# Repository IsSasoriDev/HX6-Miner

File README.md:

# HX-6

A 6 chip BM1370 Bitcoin miner board with a touchscreen, made in KiCad.

Six BM1370s (the chip from the Antminer S21 Pro) sit under one normal desktop CPU cooler, powered by a 4 phase VRM off 12 V. An ESP32-S3 runs it over WiFi and drives a 2.8" touch display.

## Specs

| | |
|---|---|
| ASICs | 6x BM1370 on one core rail |
| Expected hashrate | about 6 to 7 TH/s at stock settings |
| Power | 12 V in through XT60, around 100 to 110 W |
| Core VRM | TI TPS53647, 4 phases with CSD95490Q5MC power stages |
| Controller | ESP32-S3-WROOM-1 (N16R8), USB-C for flashing |
| Screen | Waveshare 2.8" capacitive touch LCD (ST7789 + CST328), plugs into the 13 pin GH1.25 socket |
| Cooling | any Intel LGA115x / 1200 CPU cooler, 2 PWM fan headers |
| Board | 6 layers, 170 x 115 mm |

## Status

Rev B. Fully routed, DRC clean in KiCad 7, Gerbers ready for JLCPCB.

**Not built or tested yet.** Treat it as a first prototype. If you build one, open an issue and tell me how it went.

## Layout

The board reads left to right: 12 V input, the four VRM phases, the ASIC block, then the ESP32, buttons, display socket and USB. The small 5 V, 3.3 V, 1.2 V and 0.8 V rails run along the bottom edge.

The six chips are in a 3 x 2 grid that fits inside a 46 x 46 mm square, so one cooler base covers all of them. The data chain goes 1 → 2 → 3 along the top row and comes back 4 → 5 → 6 along the bottom. Only the chips are on the top side under the cooler. All their capacitors are on the back, right under each chip.

## Schematic

Four sheets: power input and rails, core VRM, ASIC chain, and controller / display / fans.

## Files

```
hx6.kicad_pro          KiCad project (open this)
hx6.kicad_pcb          the board
*.kicad_sch            schematic sheets
hx6.kicad_sym          custom symbols
hx6.pretty/            custom footprints (BM1370, power stage, cooler hole)
fab/                   Gerber zip, BOM and CPL for JLCPCB
docs/                  images and design notes
```

It was made in KiCad 7 and opens fine in KiCad 8, 9 and 10.

## Ordering

Upload `fab/HX6_revB_gerbers_JLCPCB.zip` to JLCPCB and pick:

- 6 layers, 1.6 mm, ENIG
- 2 oz inner copper (the core rail pulls about 100 A)
- epoxy filled and capped vias. There are vias inside the chip pads and they need this.

For assembly, add `fab/HX6_revB_BOM_JLCPCB.csv` and `fab/HX6_revB_CPL_JLCPCB.csv` and match the LCSC parts in their tool. JLCPCB doesn't stock the BM1370, so you'll have to supply those or solder them yourself. Check the part rotations in their preview, especially on the bottom side.

## Before you order

- Run DRC once more in your KiCad version.
- The VRM compensation values are a starting point. Check the core rail at low load before you put real load on it.
- The 25 MHz oscillator has to be a 1.2 V part (Taitien OXLTDLJANF-25.000000 or similar).
- R20 is not fitted on purpose. VR_HOT on the VRM controller isn't used.

## Firmware

AxeForge is the default but [ESP-Miner-NerdQAxePlus](https://github.com/shufps/ESP-Miner-NerdQAxePlus) also supports 6x BM1370 with the same TPS53647 VRM, so a port mostly needs this board's pin map (in [docs/design-notes.md](docs/design-notes.md)) and drivers for the 2.8" screen and the CST328 touch chip.

## Credits

Bitmain doesn't publish a BM1370 datasheet. The pin map and footprint come from the open hardware work in [shufps/qaxe](https://github.com/shufps/qaxe) (NerdQAxe++). Check their license if you reuse those parts. The rest of the board was designed for this project.

Full technical notes (pin map, I2C addresses, layer stack, part choices) are in [docs/design-notes.md](docs/design-notes.md).

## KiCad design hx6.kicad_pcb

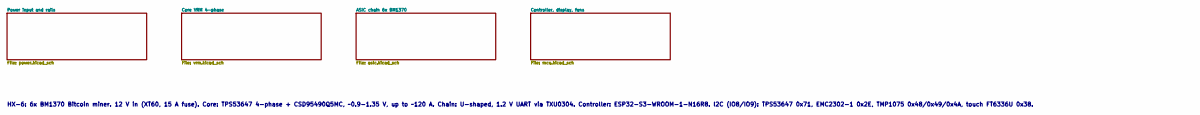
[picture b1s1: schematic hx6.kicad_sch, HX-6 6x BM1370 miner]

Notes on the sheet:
HX-6: 6x BM1370 Bitcoin miner. 12 V in (XT60, 15 A fuse). Core: TPS53647 4-phase + CSD95490Q5MC, ~0.9-1.35 V, up to ~120 A. Chain: U-shaped, 1.2 V UART via TXU0304. Controller: ESP32-S3-WROOM-1-N16R8. I2C (IO8/IO9): TPS53647 0x71, EMC2302-1 0x2E, TMP1075 0x48/0x49/0x4A, touch FT6336U 0x38.

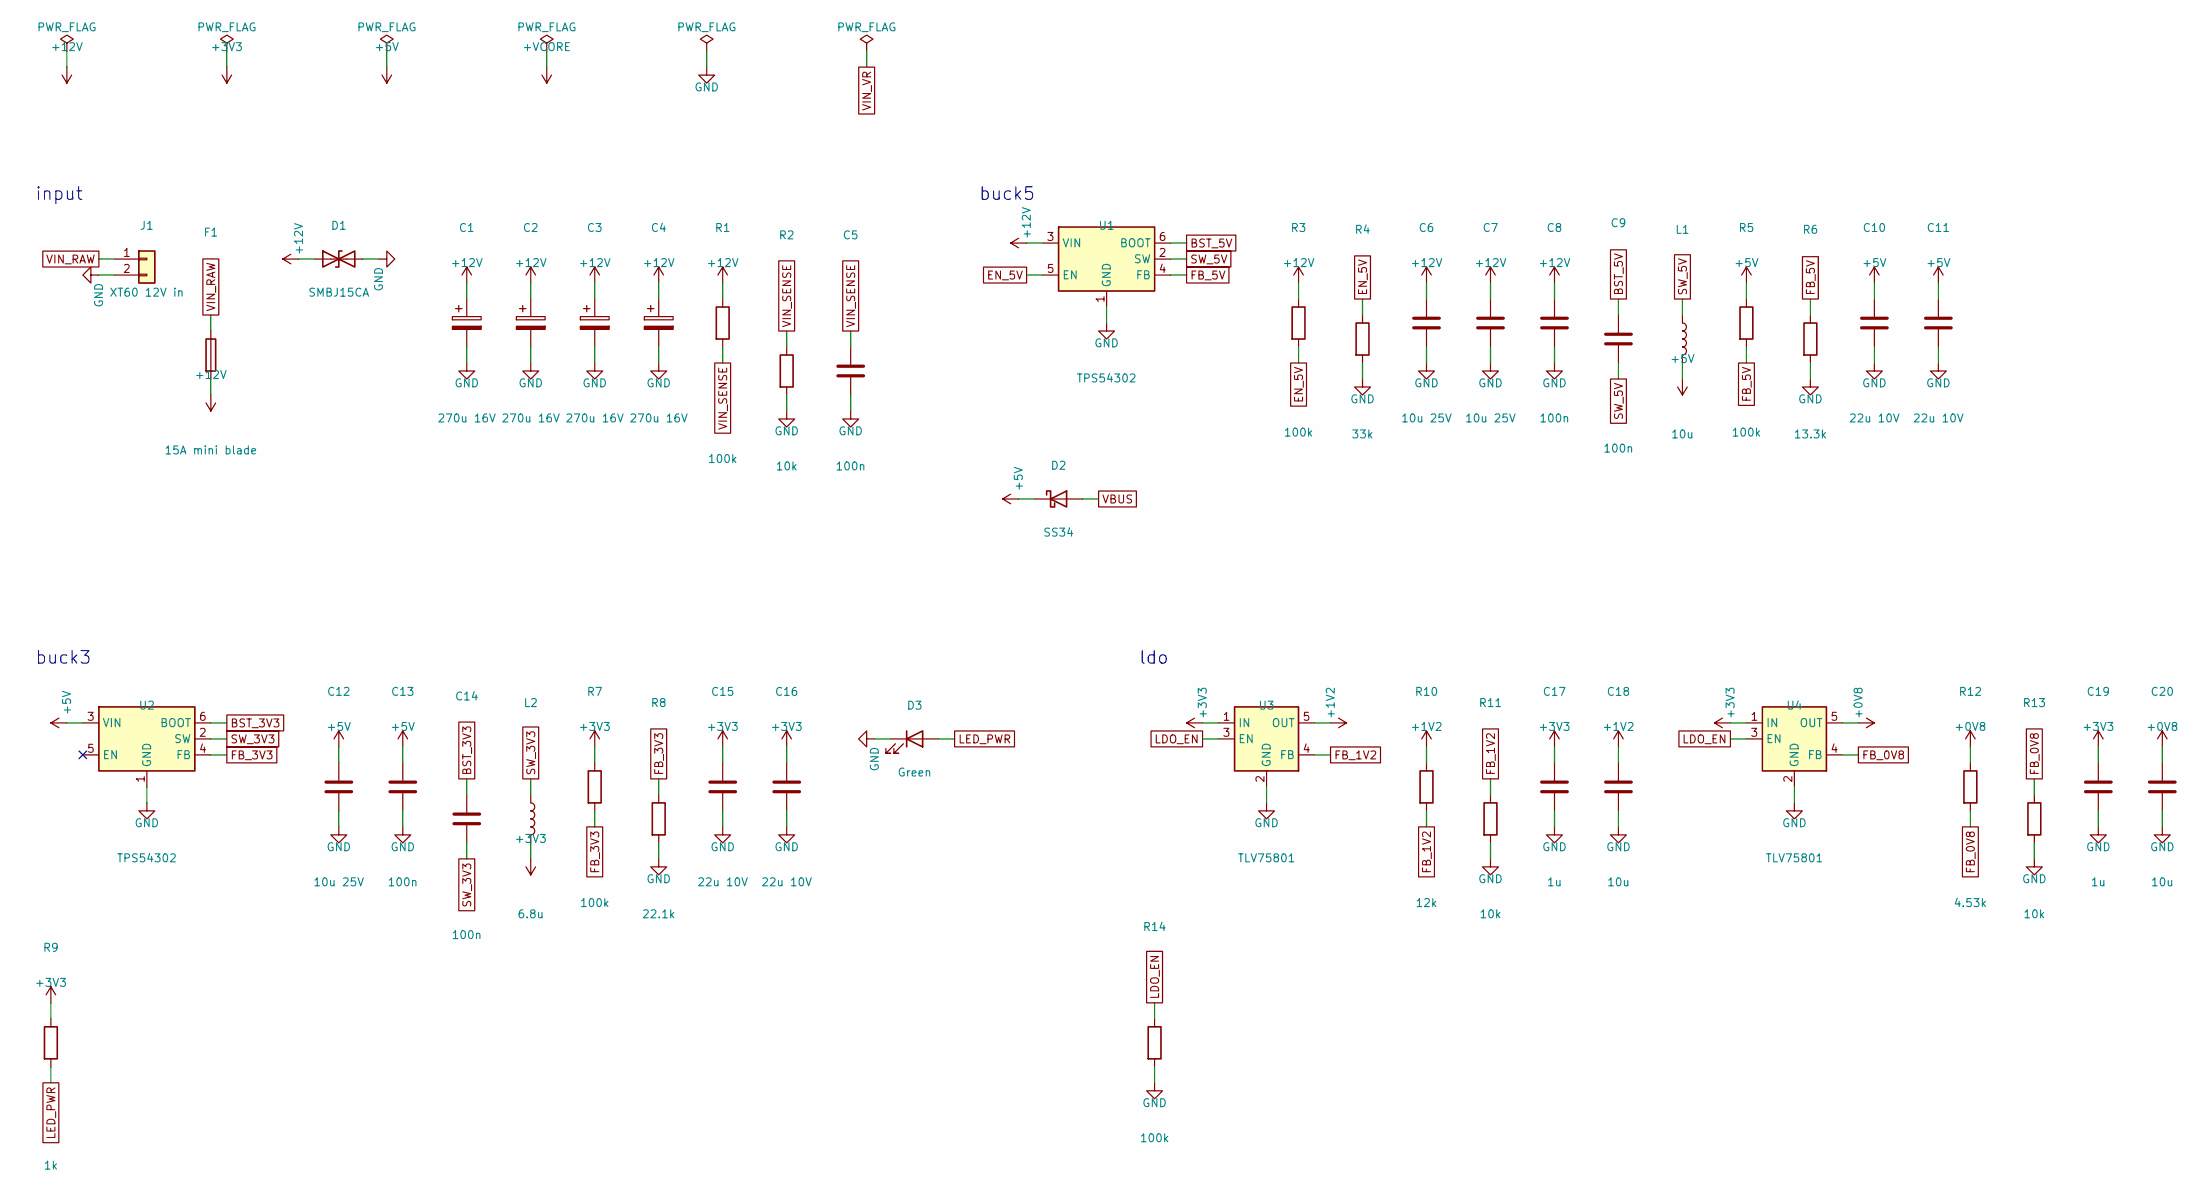
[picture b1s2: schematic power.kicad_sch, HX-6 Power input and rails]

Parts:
C1, C2, C3, C4: 270u 16V; CP_Elec_8x10; MPN Panasonic 16SVPF270M (polymer)
C5, C8, C9, C13, C14: 100n; C_0402_1005Metric
C6, C7, C12: 10u 25V; C_1206_3216Metric
C10, C11, C15, C16: 22u 10V; C_0805_2012Metric
C17, C19: 1u; C_0603_1608Metric
C18, C20: 10u; C_0805_2012Metric
D1: SMBJ15CA; D_SMB; MPN SMBJ15CA (bidirectional)
D2: SS34; D_SMA; MPN SS34
D3: Green; LED_0603_1608Metric
F1: 15A mini blade; Fuseholder_Blade_Mini_Keystone_3568; MPN Keystone 3568 holder + 15 A mini blade 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
J1: XT60 12V in; AMASS_XT60-M_1x02_P7.20mm_Vertical; MPN AMASS XT60PW-M (vertical)
L1: 10u; L_Bourns_SRP7028A_7.3x6.6mm; MPN Bourns SRP7028A-100M
L2: 6.8u; L_Bourns_SRP7028A_7.3x6.6mm; MPN Bourns SRP7028A-6R8M
R1, R3, R5, R7, R14: 100k; R_0402_1005Metric
R2, R11, R13: 10k; R_0402_1005Metric
R4: 33k; R_0402_1005Metric
R6: 13.3k; R_0402_1005Metric
R8: 22.1k; R_0402_1005Metric
R9: 1k; R_0402_1005Metric
R10: 12k; R_0402_1005Metric
R12: 4.53k; R_0402_1005Metric
U1, U2: TPS54302; SOT-23-6; MPN TPS54302DDCR
U3, U4: TLV75801; SOT-23-5; MPN TLV75801PDBVR

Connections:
+0V8: C20.1, R12.1, U4.5 (OUT); also elsewhere on the board
+1V2: C18.1, R10.1, U3.5 (OUT); also elsewhere on the board
+3V3: C15.1, C16.1, C17.1, C19.1, L2.2, R7.1, R9.1, U3.1 (IN), U4.1 (IN); also elsewhere on the board
+5V: C10.1, C11.1, C12.1, C13.1, D2.1 (K), L1.2, R5.1, U2.3 (VIN); also elsewhere on the board
+12V: C1.1, C2.1, C3.1, C4.1, C6.1, C7.1, C8.1, D1.1 (A1), F1.2, R1.1, R3.1, U1.3 (VIN); also elsewhere on the board
BST_3V3: C14.1, U2.6 (BOOT)
BST_5V: C9.1, U1.6 (BOOT)
EN_5V: R3.2, R4.1, U1.5 (EN)
FB_0V8: R12.2, R13.1, U4.4 (FB)
FB_1V2: R10.2, R11.1, U3.4 (FB)
FB_3V3: R7.2, R8.1, U2.4 (FB)
FB_5V: R5.2, R6.1, U1.4 (FB)
GND: C1.2, C2.2, C3.2, C4.2, C5.2, C6.2, C7.2, C8.2, C10.2, C11.2, C12.2, C13.2, C15.2, C16.2, C17.2, C18.2, C19.2, C20.2, D1.2 (A2), D3.1 (K), J1.2, R2.2, R4.2, R6.2, R8.2, R11.2, R13.2, R14.2, U1.1 (GND), U2.1 (GND), U3.2 (GND), U4.2 (GND); also elsewhere on the board
LDO_EN: R14.1, U3.3 (EN), U4.3 (EN); also elsewhere on the board
LED_PWR: D3.2 (A), R9.2
SW_3V3: C14.2, L2.1, U2.2 (SW)
SW_5V: C9.2, L1.1, U1.2 (SW)
VBUS: D2.2 (A); also elsewhere on the board
VIN_RAW: F1.1, J1.1
VIN_SENSE: C5.1, R1.2, R2.1; also elsewhere on the board

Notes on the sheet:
input
buck5
buck3
ldo

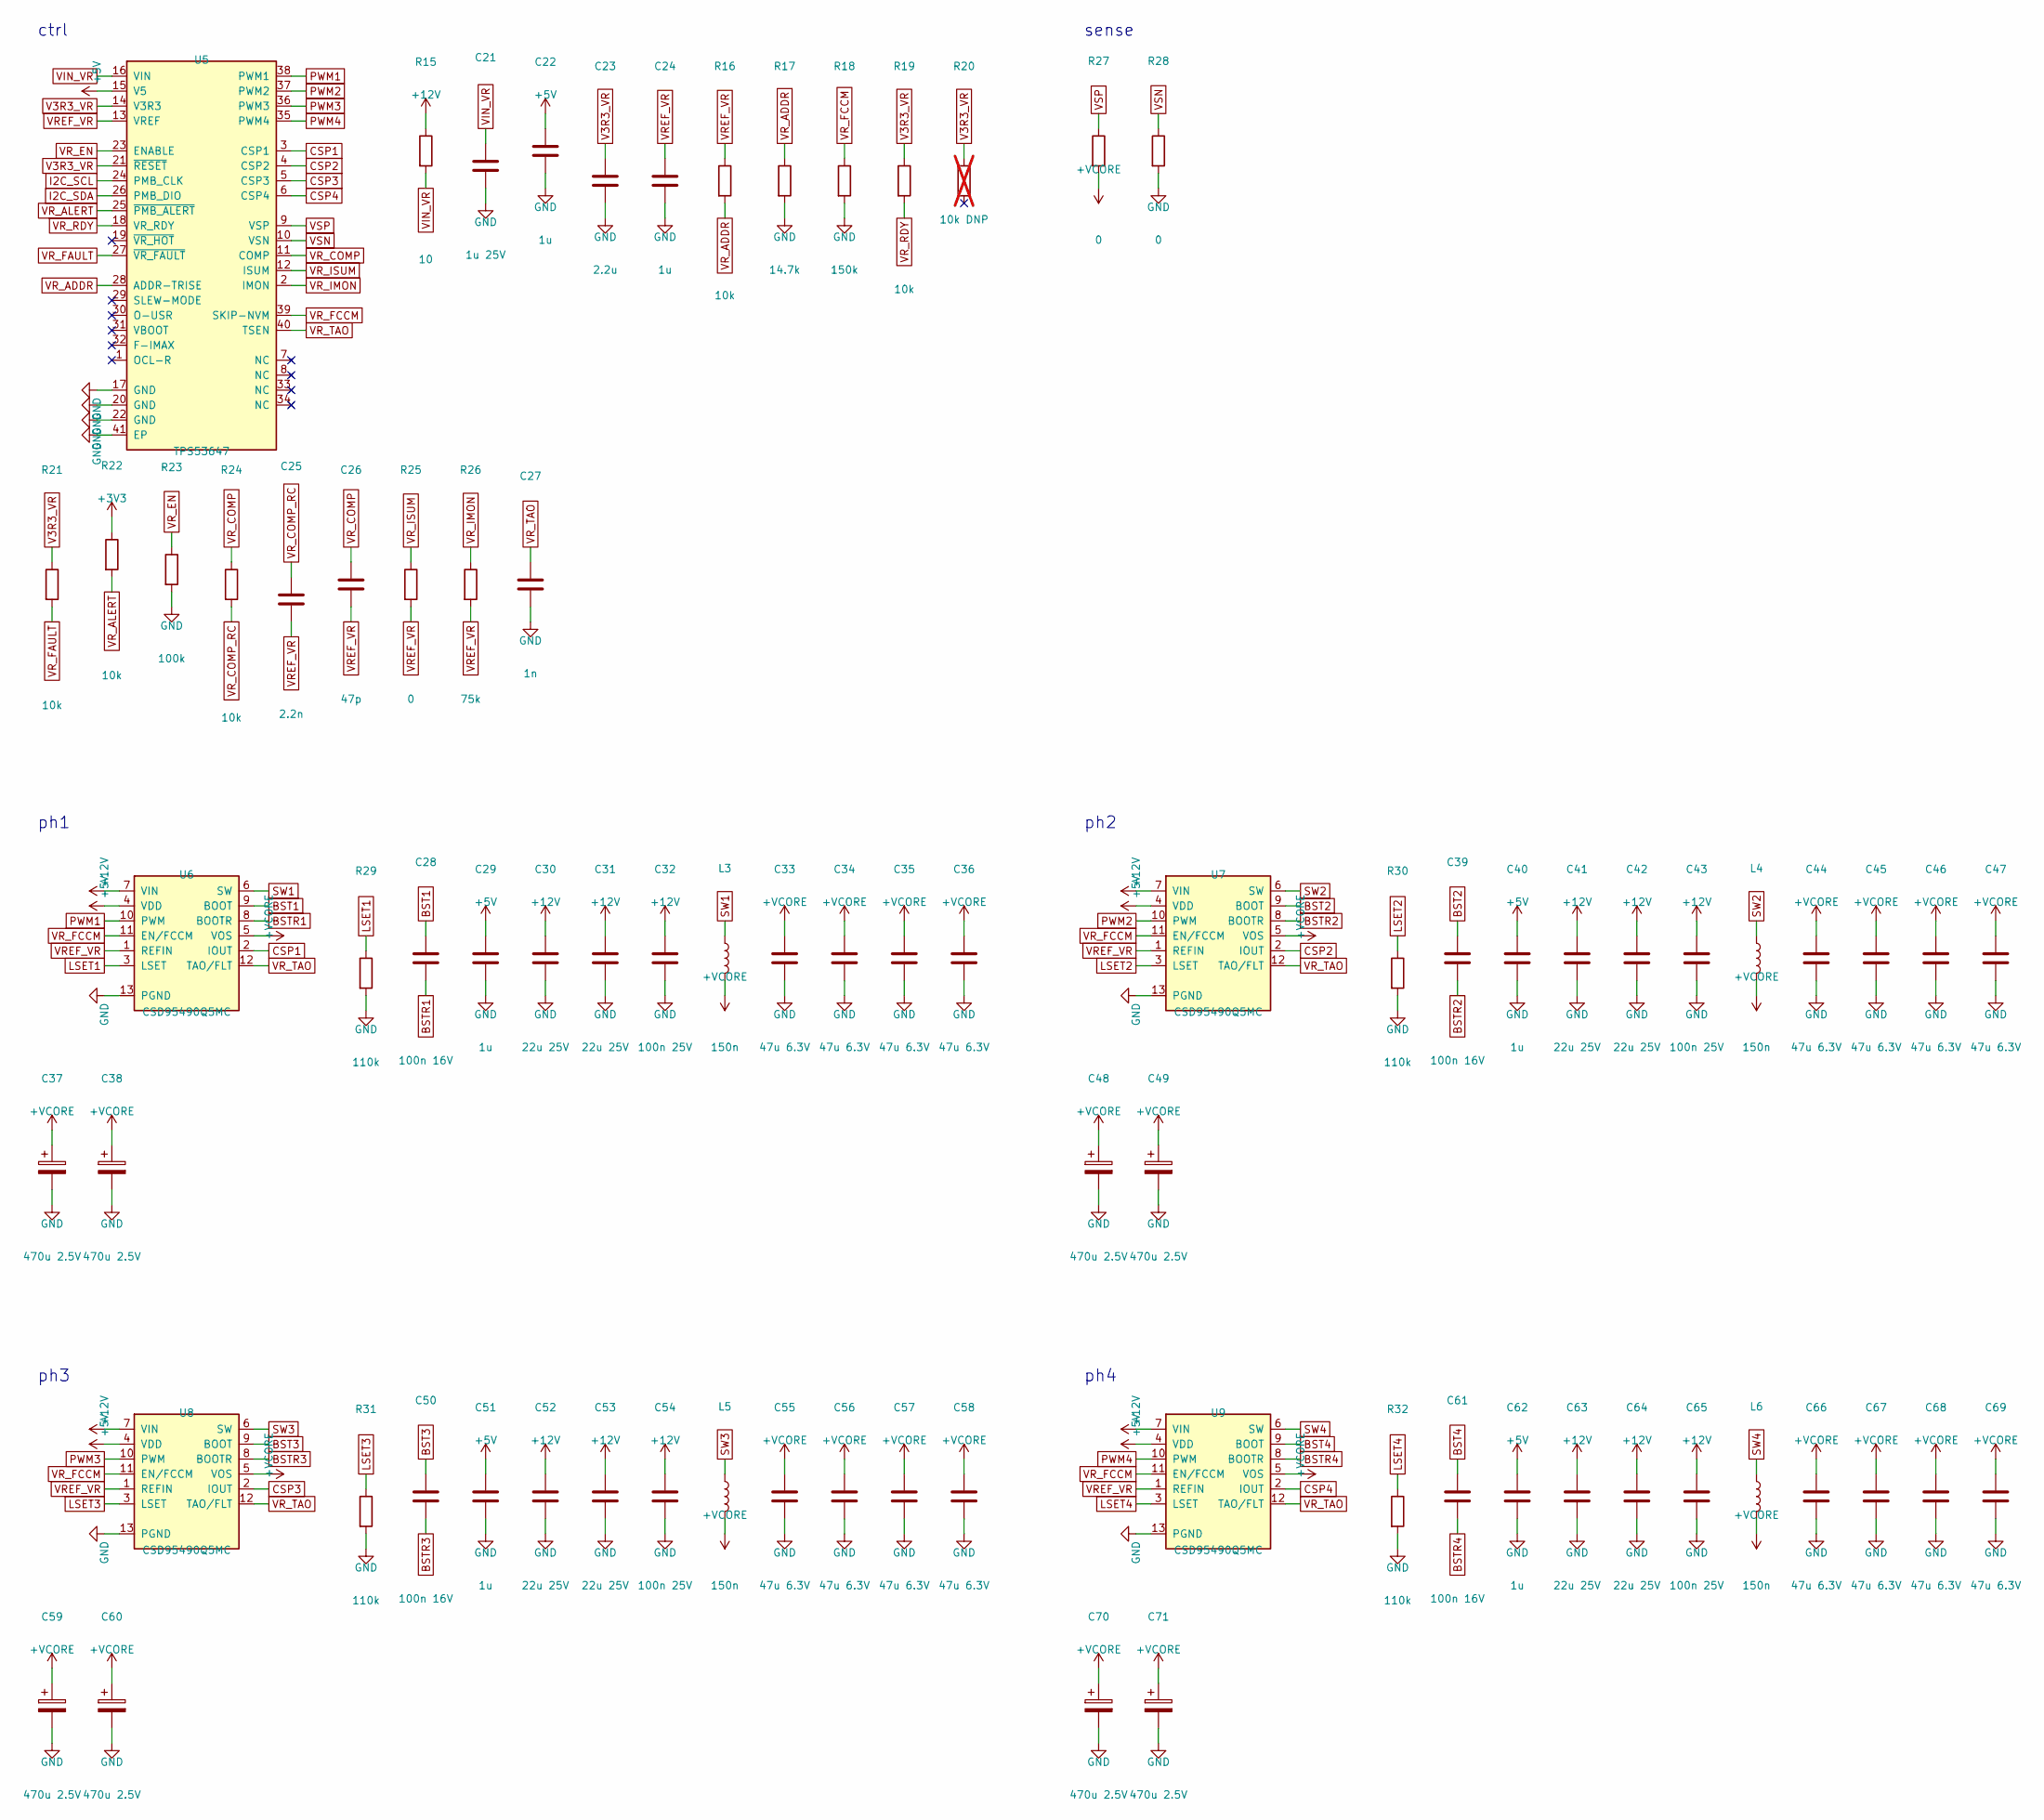
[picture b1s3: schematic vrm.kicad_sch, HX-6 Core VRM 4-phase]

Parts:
C21: 1u 25V; C_0603_1608Metric
C22, C24, C29, C40, C51, C62: 1u; C_0603_1608Metric
C23: 2.2u; C_0603_1608Metric
C25: 2.2n; C_0402_1005Metric
C26: 47p; C_0402_1005Metric
C27: 1n; C_0402_1005Metric
C28, C39, C50, C61: 100n 16V; C_0402_1005Metric
C30, C31, C41, C42, C52, C53, C63, C64: 22u 25V; C_1210_3225Metric
C32, C43, C54, C65: 100n 25V; C_0402_1005Metric
C33, C34, C35, C36, C44, C45, C46, C47, C55, C56, C57, C58, C66, C67, C68, C69: 47u 6.3V; C_1206_3216Metric
C37, C38, C48, C49, C59, C60, C70, C71: 470u 2.5V; CP_EIA-7343-31_Kemet-D; MPN Panasonic 2R5TPF470M6L (POSCAP)
L3, L4, L5, L6: 150n; L_Coilcraft_XAL7070-XXX; MPN Coilcraft XAL7070-151MEC
R15: 10; R_0603_1608Metric
R16, R19, R21, R22, R24: 10k; R_0402_1005Metric
R17: 14.7k; R_0402_1005Metric
R18: 150k; R_0402_1005Metric
R20: 10k DNP; R_0402_1005Metric; not fitted
R23: 100k; R_0402_1005Metric
R25, R27, R28: 0; R_0402_1005Metric
R26: 75k; R_0402_1005Metric
R29, R30, R31, R32: 110k; R_0402_1005Metric
U5: TPS53647; Texas_RHA0040B_VQFN-40-1EP_6x6mm_P0.5mm_EP4.15x4.15mm_Therm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; MPN TPS53647RTAR
U6, U7, U8, U9: CSD95490Q5MC; TI_DMC0012A_VSON-CLIP_5x6mm; MPN CSD95490Q5MC

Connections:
+3V3: R22.1; also elsewhere on the board
+5V: C22.1, C29.1, C40.1, C51.1, C62.1, U5.15 (V5), U6.4 (VDD), U7.4 (VDD), U8.4 (VDD), U9.4 (VDD); also elsewhere on the board
+12V: C30.1, C31.1, C32.1, C41.1, C42.1, C43.1, C52.1, C53.1, C54.1, C63.1, C64.1, C65.1, R15.1, U6.7 (VIN), U7.7 (VIN), U8.7 (VIN), U9.7 (VIN); also elsewhere on the board
+VCORE: C33.1, C34.1, C35.1, C36.1, C37.1, C38.1, C44.1, C45.1, C46.1, C47.1, C48.1, C49.1, C55.1, C56.1, C57.1, C58.1, C59.1, C60.1, C66.1, C67.1, C68.1, C69.1, C70.1, C71.1, L3.2, L4.2, L5.2, L6.2, R27.2, U6.5 (VOS), U7.5 (VOS), U8.5 (VOS), U9.5 (VOS); also elsewhere on the board
BST1: C28.1, U6.9 (BOOT)
BST2: C39.1, U7.9 (BOOT)
BST3: C50.1, U8.9 (BOOT)
BST4: C61.1, U9.9 (BOOT)
BSTR1: C28.2, U6.8 (BOOTR)
BSTR2: C39.2, U7.8 (BOOTR)
BSTR3: C50.2, U8.8 (BOOTR)
BSTR4: C61.2, U9.8 (BOOTR)
CSP1: U5.3 (CSP1), U6.2 (IOUT)
CSP2: U5.4 (CSP2), U7.2 (IOUT)
CSP3: U5.5 (CSP3), U8.2 (IOUT)
CSP4: U5.6 (CSP4), U9.2 (IOUT)
GND: C21.2, C22.2, C23.2, C24.2, C27.2, C29.2, C30.2, C31.2, C32.2, C33.2, C34.2, C35.2, C36.2, C37.2, C38.2, C40.2, C41.2, C42.2, C43.2, C44.2, C45.2, C46.2, C47.2, C48.2, C49.2, C51.2, C52.2, C53.2, C54.2, C55.2, C56.2, C57.2, C58.2, C59.2, C60.2, C62.2, C63.2, C64.2, C65.2, C66.2, C67.2, C68.2, C69.2, C70.2, C71.2, R17.2, R18.2, R23.2, R28.2, R29.2, R30.2, R31.2, R32.2, U5.17 (GND), U5.20 (GND), U5.22 (GND), U5.41 (EP), U6.13 (PGND), U7.13 (PGND), U8.13 (PGND), U9.13 (PGND); also elsewhere on the board
I2C_SCL: U5.24 (PMB_CLK); also elsewhere on the board
I2C_SDA: U5.26 (PMB_DIO); also elsewhere on the board
LSET1: R29.1, U6.3 (LSET)
LSET2: R30.1, U7.3 (LSET)
LSET3: R31.1, U8.3 (LSET)
LSET4: R32.1, U9.3 (LSET)
PWM1: U5.38 (PWM1), U6.10 (PWM)
PWM2: U5.37 (PWM2), U7.10 (PWM)
PWM3: U5.36 (PWM3), U8.10 (PWM)
PWM4: U5.35 (PWM4), U9.10 (PWM)
SW1: L3.1, U6.6 (SW)
SW2: L4.1, U7.6 (SW)
SW3: L5.1, U8.6 (SW)
SW4: L6.1, U9.6 (SW)
V3R3_VR: C23.1, R19.1, R20.1, R21.1, U5.14 (V3R3), U5.21 (~RESET)
VIN_VR: C21.1, R15.2, U5.16 (VIN)
VREF_VR: C24.1, C25.2, C26.2, R16.1, R25.2, R26.2, U5.13 (VREF), U6.1 (REFIN), U7.1 (REFIN), U8.1 (REFIN), U9.1 (REFIN)
VR_ADDR: R16.2, R17.1, U5.28 (ADDR-TRISE)
VR_ALERT: R22.2, U5.25 (~PMB_ALERT); also elsewhere on the board
VR_COMP: C26.1, R24.1, U5.11 (COMP)
VR_COMP_RC: C25.1, R24.2
VR_EN: R23.1, U5.23 (ENABLE); also elsewhere on the board
VR_FAULT: R21.2, U5.27 (~VR_FAULT)
VR_FCCM: R18.1, U5.39 (SKIP-NVM), U6.11 (EN/FCCM), U7.11 (EN/FCCM), U8.11 (EN/FCCM), U9.11 (EN/FCCM)
VR_IMON: R26.1, U5.2 (IMON)
VR_ISUM: R25.1, U5.12 (ISUM)
VR_RDY: R19.2, U5.18 (VR_RDY); also elsewhere on the board
VR_TAO: C27.1, U5.40 (TSEN), U6.12 (TAO/FLT), U7.12 (TAO/FLT), U8.12 (TAO/FLT), U9.12 (TAO/FLT)
VSN: R28.1, U5.10 (VSN)
VSP: R27.1, U5.9 (VSP)

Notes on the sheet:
ctrl
sense
ph1
ph2
ph3
ph4

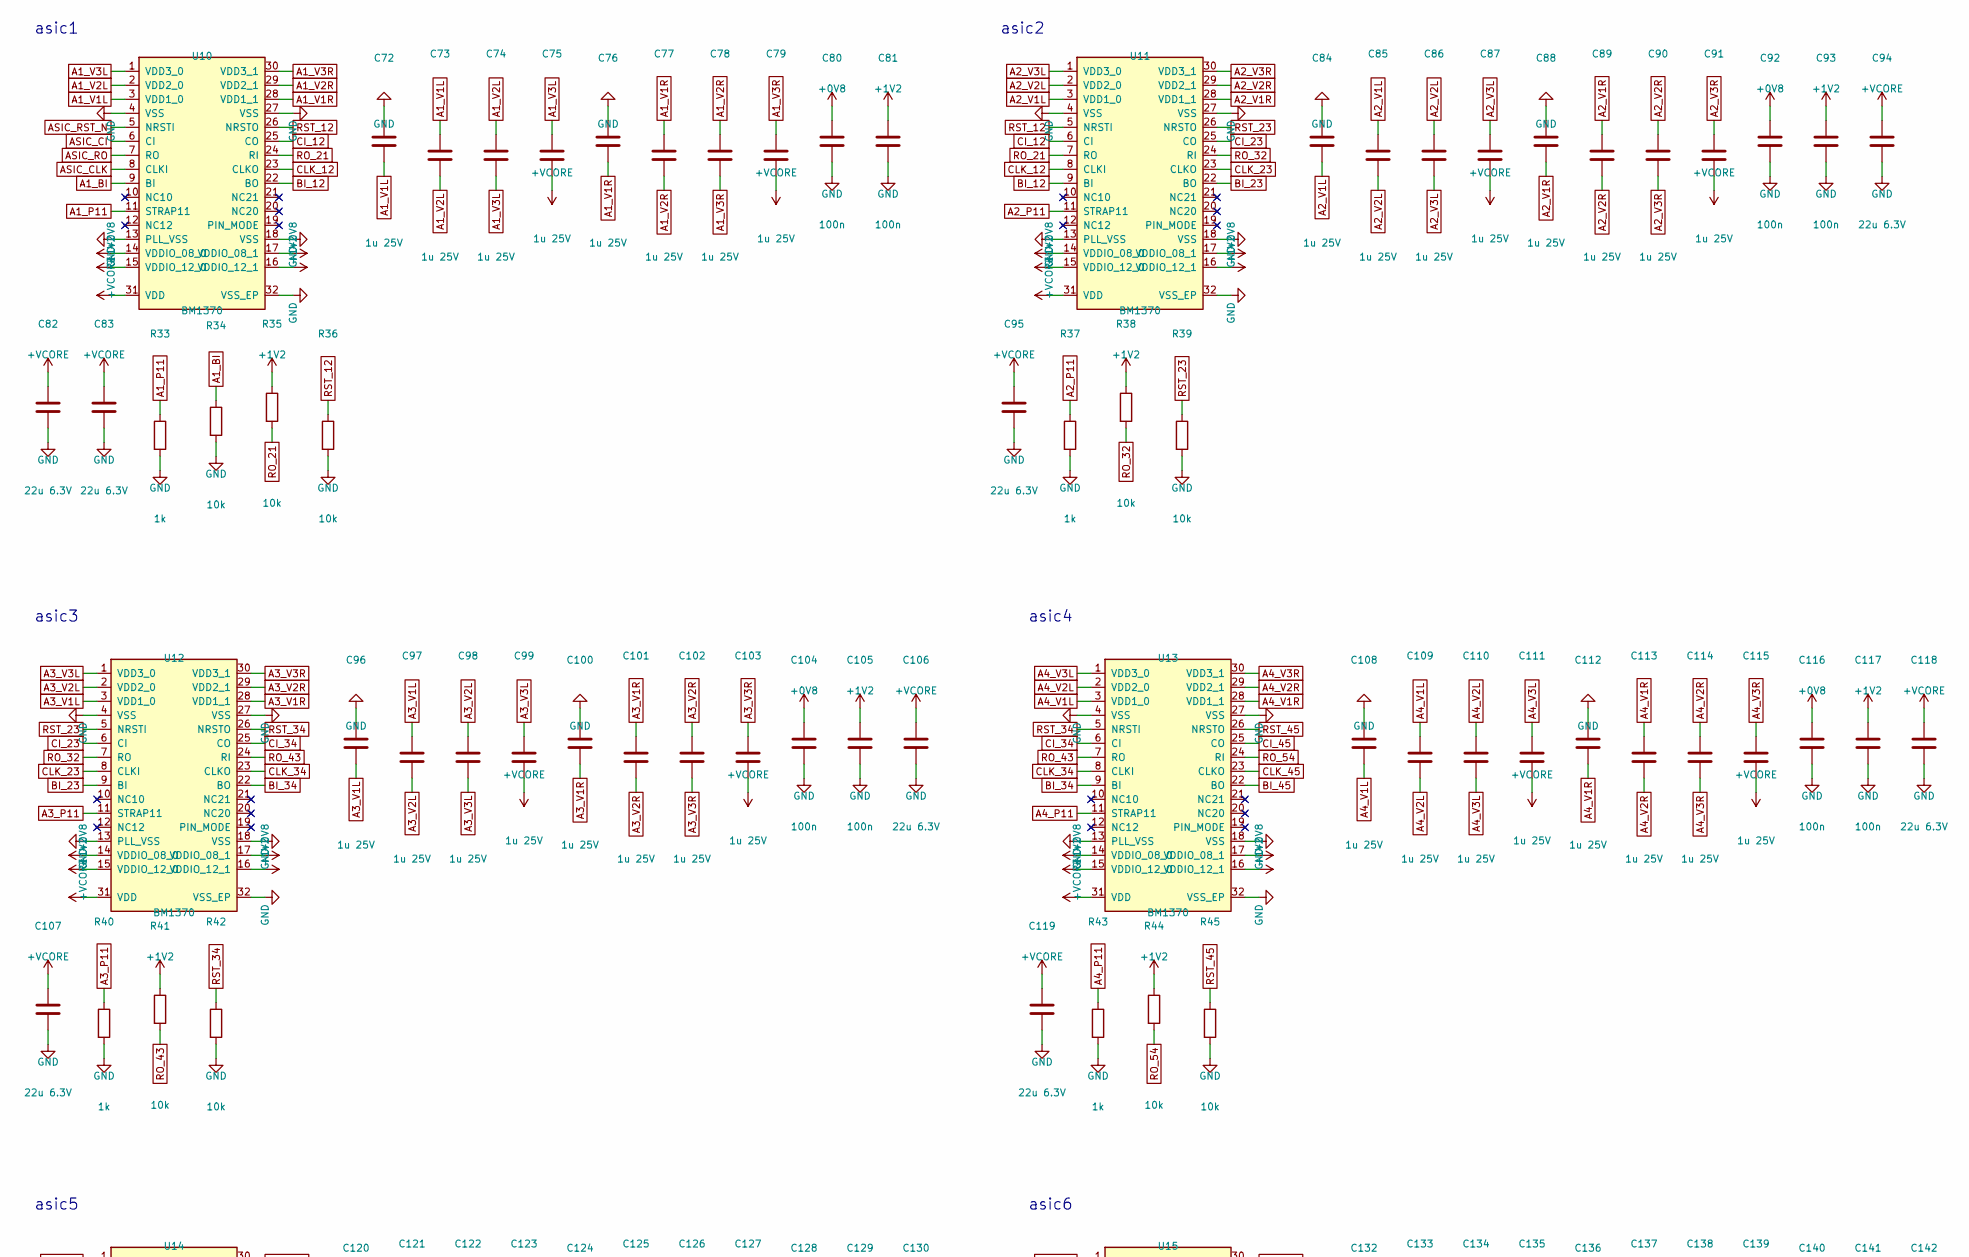
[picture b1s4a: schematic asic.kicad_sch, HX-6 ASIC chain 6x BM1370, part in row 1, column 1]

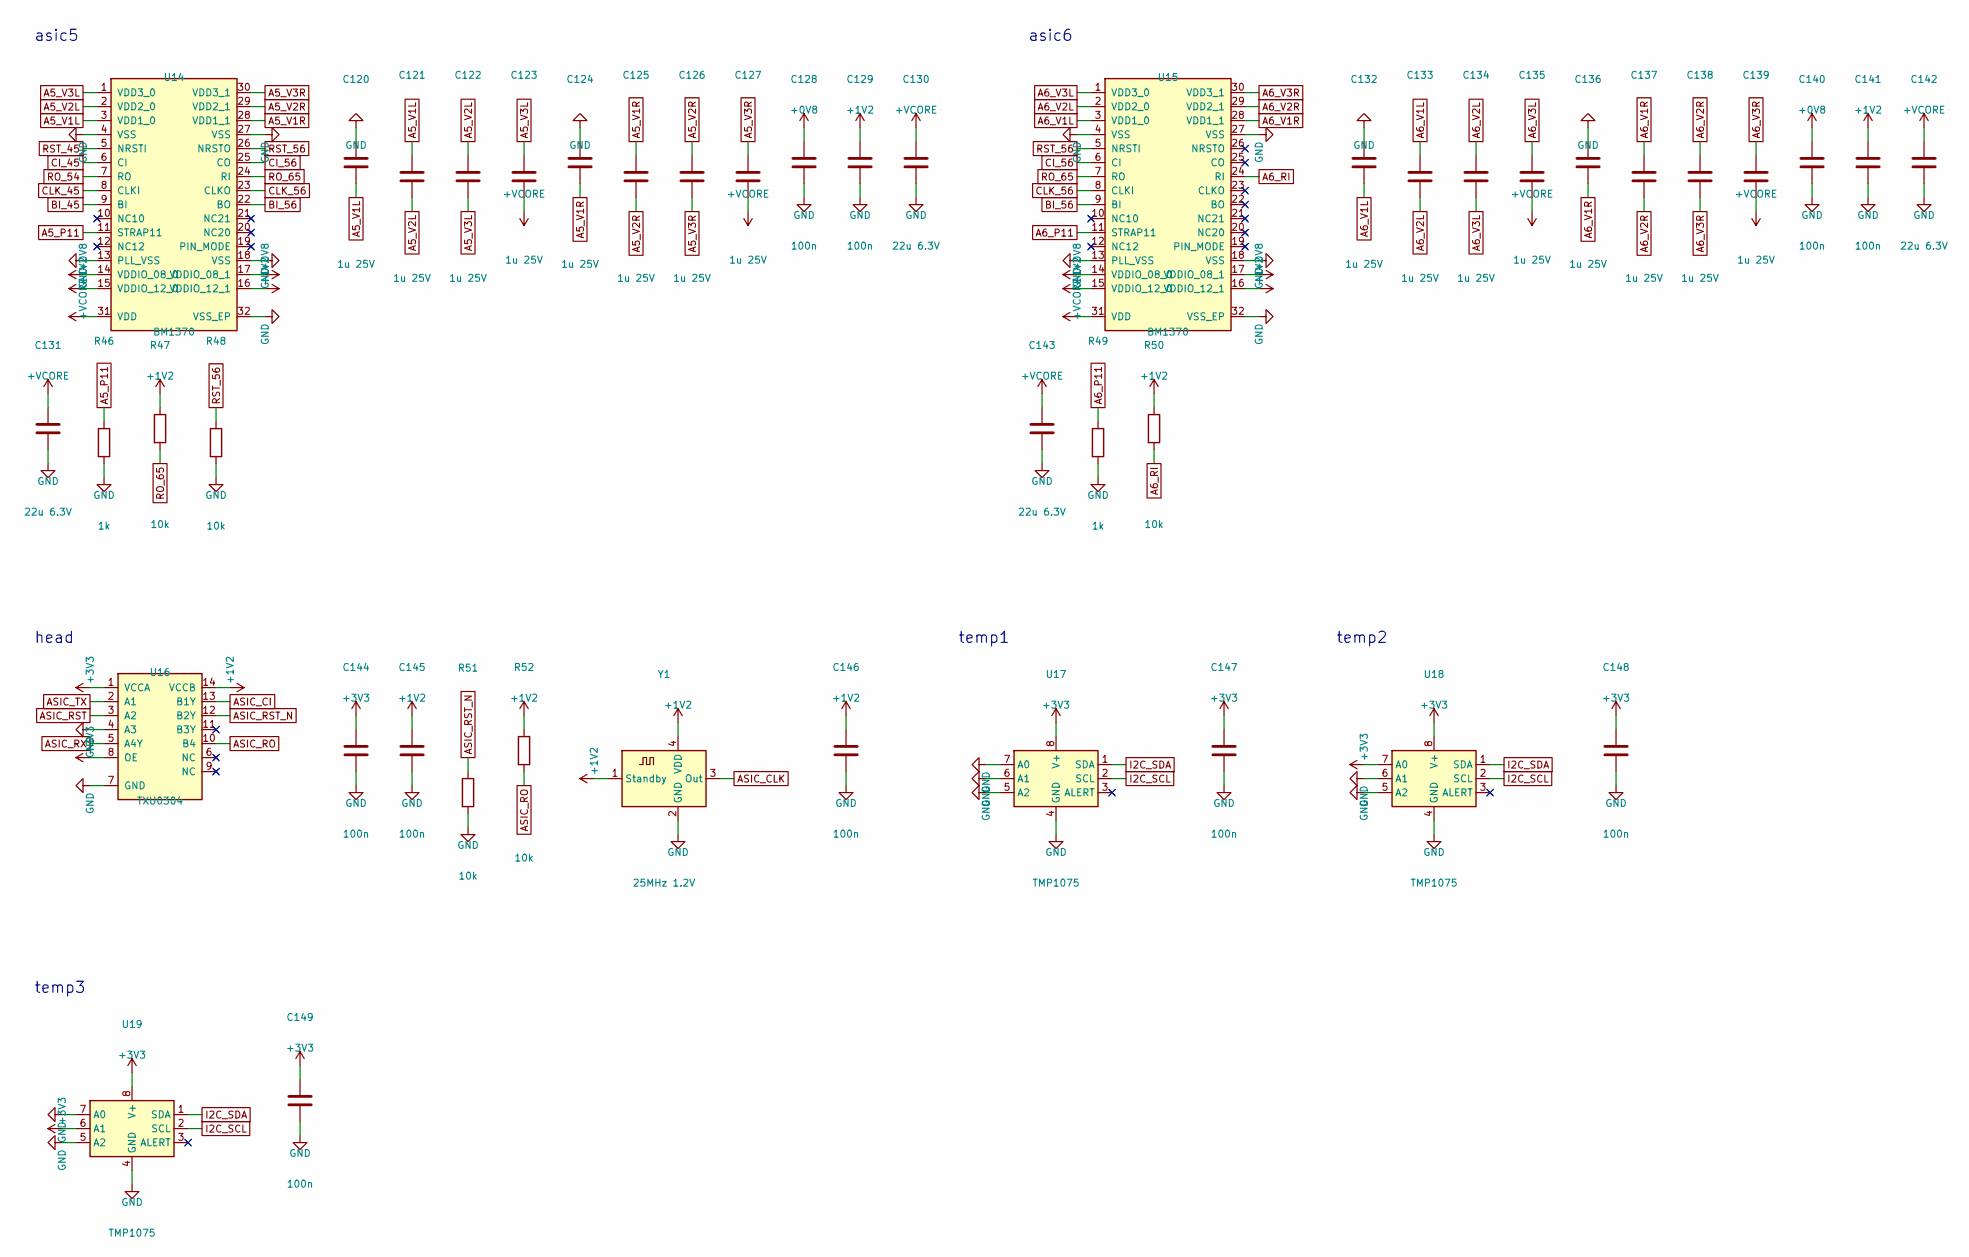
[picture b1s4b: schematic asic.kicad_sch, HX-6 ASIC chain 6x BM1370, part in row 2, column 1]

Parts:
C72, C73, C74, C75, C76, C77, C78, C79, C84, C85, C86, C87, C88, C89, C90, C91, C96, C97, C98, C99, C100, C101, C102, C103, C108, C109, C110, C111, C112, C113, C114, C115, C120, C121, C122, C123, C124, C125, C126, C127, C132, C133, C134, C135, C136, C137, C138, C139: 1u 25V; C_0402_1005Metric
C80, C81, C92, C93, C104, C105, C116, C117, C128, C129, C140, C141, C144, C145, C146, C147, C148, C149: 100n; C_0402_1005Metric
C82, C83, C94, C95, C106, C107, C118, C119, C130, C131, C142, C143: 22u 6.3V; C_0805_2012Metric
R33, R37, R40, R43, R46, R49: 1k; R_0402_1005Metric
R34, R35, R36, R38, R39, R41, R42, R44, R45, R47, R48, R50, R51, R52: 10k; R_0402_1005Metric
U10, U11, U12, U13, U14, U15: BM1370; MPN Bitmain BM1370
U16: TXU0304; TSSOP-14_4.4x5mm_P0.65mm; MPN TXU0304PWR
U17, U18, U19: TMP1075; SO-8_3.9x4.9mm_P1.27mm; MPN TMP1075DR
Y1: 25MHz 1.2V; Oscillator_SMD_Abracon_ASE-4Pin_3.2x2.5mm; MPN Taitien OXLTDLJANF-25.000000 (1.2 V CMO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

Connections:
+0V8: C80.1, C92.1, C104.1, C116.1, C128.1, C140.1, U10.14 (VDDIO_08_0), U10.17 (VDDIO_08_1), U11.14 (VDDIO_08_0), U11.17 (VDDIO_08_1), U12.14 (VDDIO_08_0), U12.17 (VDDIO_08_1), U13.14 (VDDIO_08_0), U13.17 (VDDIO_08_1), U14.14 (VDDIO_08_0), U14.17 (VDDIO_08_1), U15.14 (VDDIO_08_0), U15.17 (VDDIO_08_1); also elsewhere on the board
+1V2: C81.1, C93.1, C105.1, C117.1, C129.1, C141.1, C145.1, C146.1, R35.1, R38.1, R41.1, R44.1, R47.1, R50.1, R52.1, U10.15 (VDDIO_12_0), U10.16 (VDDIO_12_1), U11.15 (VDDIO_12_0), U11.16 (VDDIO_12_1), U12.15 (VDDIO_12_0), U12.16 (VDDIO_12_1), U13.15 (VDDIO_12_0), U13.16 (VDDIO_12_1), U14.15 (VDDIO_12_0), U14.16 (VDDIO_12_1), U15.15 (VDDIO_12_0), U15.16 (VDDIO_12_1), U16.14 (VCCB), Y1.1 (Standby), Y1.4 (VDD); also elsewhere on the board
+3V3: C144.1, C147.1, C148.1, C149.1, U16.1 (VCCA), U16.8 (OE), U17.8 (V+), U18.7 (A0), U18.8 (V+), U19.6 (A1), U19.8 (V+); also elsewhere on the board
+VCORE: C75.2, C79.2, C82.1, C83.1, C87.2, C91.2, C94.1, C95.1, C99.2, C103.2, C106.1, C107.1, C111.2, C115.2, C118.1, C119.1, C123.2, C127.2, C130.1, C131.1, C135.2, C139.2, C142.1, C143.1, U10.31 (VDD), U11.31 (VDD), U12.31 (VDD), U13.31 (VDD), U14.31 (VDD), U15.31 (VDD); also elsewhere on the board
A1_BI: R34.1, U10.9 (BI)
A1_P11: R33.1, U10.11 (STRAP11)
A1_V1L: C72.2, C73.1, U10.3 (VDD1_0)
A1_V1R: C76.2, C77.1, U10.28 (VDD1_1)
A1_V2L: C73.2, C74.1, U10.2 (VDD2_0)
A1_V2R: C77.2, C78.1, U10.29 (VDD2_1)
A1_V3L: C74.2, C75.1, U10.1 (VDD3_0)
A1_V3R: C78.2, C79.1, U10.30 (VDD3_1)
A2_P11: R37.1, U11.11 (STRAP11)
A2_V1L: C84.2, C85.1, U11.3 (VDD1_0)
A2_V1R: C88.2, C89.1, U11.28 (VDD1_1)
A2_V2L: C85.2, C86.1, U11.2 (VDD2_0)
A2_V2R: C89.2, C90.1, U11.29 (VDD2_1)
A2_V3L: C86.2, C87.1, U11.1 (VDD3_0)
A2_V3R: C90.2, C91.1, U11.30 (VDD3_1)
A3_P11: R40.1, U12.11 (STRAP11)
A3_V1L: C96.2, C97.1, U12.3 (VDD1_0)
A3_V1R: C100.2, C101.1, U12.28 (VDD1_1)
A3_V2L: C97.2, C98.1, U12.2 (VDD2_0)
A3_V2R: C101.2, C102.1, U12.29 (VDD2_1)
A3_V3L: C98.2, C99.1, U12.1 (VDD3_0)
A3_V3R: C102.2, C103.1, U12.30 (VDD3_1)
A4_P11: R43.1, U13.11 (STRAP11)
A4_V1L: C108.2, C109.1, U13.3 (VDD1_0)
A4_V1R: C112.2, C113.1, U13.28 (VDD1_1)
A4_V2L: C109.2, C110.1, U13.2 (VDD2_0)
A4_V2R: C113.2, C114.1, U13.29 (VDD2_1)
A4_V3L: C110.2, C111.1, U13.1 (VDD3_0)
A4_V3R: C114.2, C115.1, U13.30 (VDD3_1)
A5_P11: R46.1, U14.11 (STRAP11)
A5_V1L: C120.2, C121.1, U14.3 (VDD1_0)
A5_V1R: C124.2, C125.1, U14.28 (VDD1_1)
A5_V2L: C121.2, C122.1, U14.2 (VDD2_0)
A5_V2R: C125.2, C126.1, U14.29 (VDD2_1)
A5_V3L: C122.2, C123.1, U14.1 (VDD3_0)
A5_V3R: C126.2, C127.1, U14.30 (VDD3_1)
A6_P11: R49.1, U15.11 (STRAP11)
A6_RI: R50.2, U15.24 (RI)
A6_V1L: C132.2, C133.1, U15.3 (VDD1_0)
A6_V1R: C136.2, C137.1, U15.28 (VDD1_1)
A6_V2L: C133.2, C134.1, U15.2 (VDD2_0)
A6_V2R: C137.2, C138.1, U15.29 (VDD2_1)
A6_V3L: C134.2, C135.1, U15.1 (VDD3_0)
A6_V3R: C138.2, C139.1, U15.30 (VDD3_1)
ASIC_CI: U10.6 (CI), U16.13 (B1Y)
ASIC_CLK: U10.8 (CLKI), Y1.3 (Out)
ASIC_RO: R52.2, U10.7 (RO), U16.10 (B4)
ASIC_RST: U16.3 (A2); also elsewhere on the board
ASIC_RST_N: R51.1, U10.5 (NRSTI), U16.12 (B2Y)
ASIC_RX: U16.5 (A4Y); also elsewhere on the board
ASIC_TX: U16.2 (A1); also elsewhere on the board
BI_12: U10.22 (BO), U11.9 (BI)
BI_23: U11.22 (BO), U12.9 (BI)
BI_34: U12.22 (BO), U13.9 (BI)
BI_45: U13.22 (BO), U14.9 (BI)
BI_56: U14.22 (BO), U15.9 (BI)
CI_12: U10.25 (CO), U11.6 (CI)
CI_23: U11.25 (CO), U12.6 (CI)
CI_34: U12.25 (CO), U13.6 (CI)
CI_45: U13.25 (CO), U14.6 (CI)
CI_56: U14.25 (CO), U15.6 (CI)
CLK_12: U10.23 (CLKO), U11.8 (CLKI)
CLK_23: U11.23 (CLKO), U12.8 (CLKI)
CLK_34: U12.23 (CLKO), U13.8 (CLKI)
CLK_45: U13.23 (CLKO), U14.8 (CLKI)
CLK_56: U14.23 (CLKO), U15.8 (CLKI)
GND: C72.1, C76.1, C80.2, C81.2, C82.2, C83.2, C84.1, C88.1, C92.2, C93.2, C94.2, C95.2, C96.1, C100.1, C104.2, C105.2, C106.2, C107.2, C108.1, C112.1, C116.2, C117.2, C118.2, C119.2, C120.1, C124.1, C128.2, C129.2, C130.2, C131.2, C132.1, C136.1, C140.2, C141.2, C142.2, C143.2, C144.2, C145.2, C146.2, C147.2, C148.2, C149.2, R33.2, R34.2, R36.2, R37.2, R39.2, R40.2, R42.2, R43.2, R45.2, R46.2, R48.2, R49.2, R51.2, U10.4 (VSS), U10.13 (PLL_VSS), U10.18 (VSS), U10.27 (VSS), U10.32 (VSS_EP), U11.4 (VSS), U11.13 (PLL_VSS), U11.18 (VSS), U11.27 (VSS), U11.32 (VSS_EP), U12.4 (VSS), U12.13 (PLL_VSS), U12.18 (VSS), U12.27 (VSS), U12.32 (VSS_EP), U13.4 (VSS), U13.13 (PLL_VSS), U13.18 (VSS), U13.27 (VSS), U13.32 (VSS_EP), U14.4 (VSS), U14.13 (PLL_VSS), U14.18 (VSS), U14.27 (VSS), U14.32 (VSS_EP), U15.4 (VSS), U15.13 (PLL_VSS), U15.18 (VSS), U15.27 (VSS), U15.32 (VSS_EP), U16.4 (A3), U16.7 (GND), U17.4 (GND), U17.5 (A2), U17.6 (A1), U17.7 (A0), U18.4 (GND), U18.5 (A2), U18.6 (A1), U19.4 (GND), U19.5 (A2), U19.7 (A0), Y1.2 (GND); also elsewhere on the board
I2C_SCL: U17.2 (SCL), U18.2 (SCL), U19.2 (SCL); also elsewhere on the board
I2C_SDA: U17.1 (SDA), U18.1 (SDA), U19.1 (SDA); also elsewhere on the board
RO_21: R35.2, U10.24 (RI), U11.7 (RO)
RO_32: R38.2, U11.24 (RI), U12.7 (RO)
RO_43: R41.2, U12.24 (RI), U13.7 (RO)
RO_54: R44.2, U13.24 (RI), U14.7 (RO)
RO_65: R47.2, U14.24 (RI), U15.7 (RO)
RST_12: R36.1, U10.26 (NRSTO), U11.5 (NRSTI)
RST_23: R39.1, U11.26 (NRSTO), U12.5 (NRSTI)
RST_34: R42.1, U12.26 (NRSTO), U13.5 (NRSTI)
RST_45: R45.1, U13.26 (NRSTO), U14.5 (NRSTI)
RST_56: R48.1, U14.26 (NRSTO), U15.5 (NRSTI)

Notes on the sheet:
asic1
asic2
asic3
asic4
asic5
asic6
head
temp1
temp2
temp3
